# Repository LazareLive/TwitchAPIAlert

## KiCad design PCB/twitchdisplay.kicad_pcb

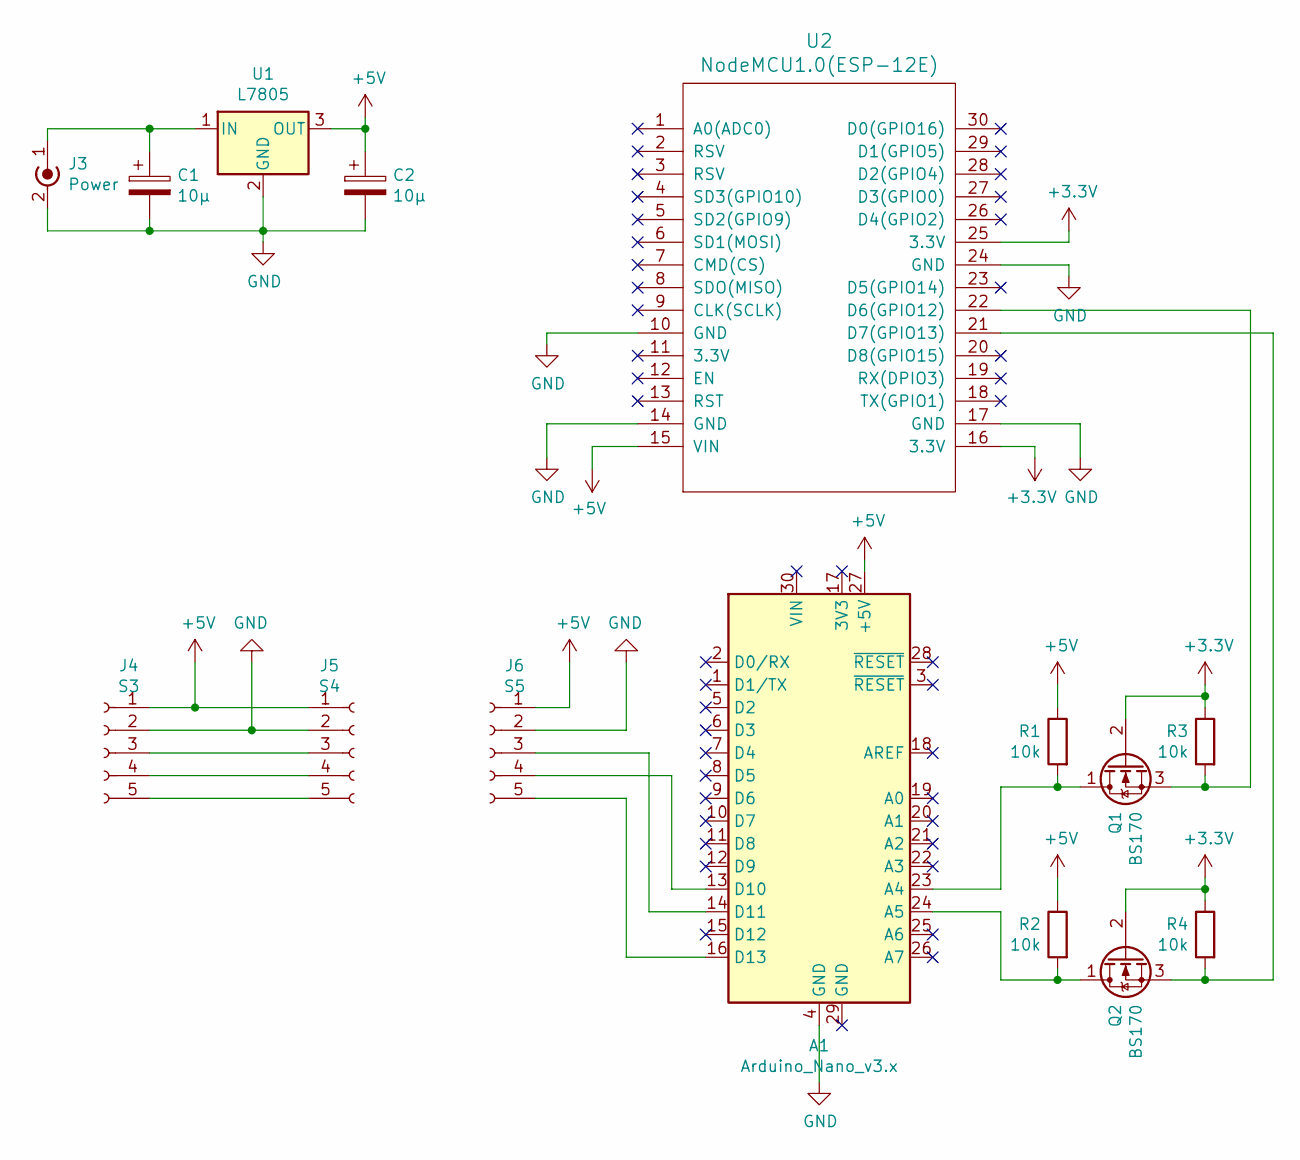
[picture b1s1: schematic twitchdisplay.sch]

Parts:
A1: Arduino_Nano_v3.x; Arduino_Nano
C1, C2: 10µ; CP_Radial_D5.0mm_P2.50mm
J3: Power; PinSocket_1x02_P2.54mm_Vertical
J4: S3; PinSocket_1x05_P2.54mm_Vertical
J5: S4; PinSocket_1x05_P2.54mm_Vertical
J6: S5; PinSocket_1x05_P2.54mm_Vertical
Q1, Q2: BS170; TO-92_Inline
R1, R2, R3, R4: 10k; R_Axial_DIN0207_L6.3mm_D2.5mm_P7.62mm_Horizontal
U1: L7805; TO-220-3_Horizontal_TabDown
U2: NodeMCU1.0(ESP-12E); NodeMCU1.0(12-E)

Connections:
+3V3: Q1.2 (G), Q2.2 (G), R3.1, R4.1, U2.16 (3.3V), U2.25 (3.3V)
+5V: A1.27 (+5V), C2.1, J4.1, J5.1, J6.1, R1.1, R2.1, U1.3 (OUT), U2.15 (VIN)
GND: A1.4 (GND), C1.2, C2.2, J3.2 (Ext), J4.2, J5.2, J6.2, U1.2 (GND), U2.10 (GND), U2.14 (GND), U2.17 (GND), U2.24 (GND)
unnamed: A1.13 (D10), J6.4
unnamed: A1.14 (D11), J6.3
unnamed: A1.16 (D13), J6.5
unnamed: A1.23 (A4), Q1.1 (D), R1.2
unnamed: A1.24 (A5), Q2.1 (D), R2.2
unnamed: C1.1, J3.1 (In), U1.1 (IN)
unnamed: J4.3, J5.3
unnamed: J4.4, J5.4
unnamed: J4.5, J5.5
unnamed: Q1.3 (S), R3.2, U2.22 (D6(GPIO12))
unnamed: Q2.3 (S), R4.2, U2.21 (D7(GPIO13))

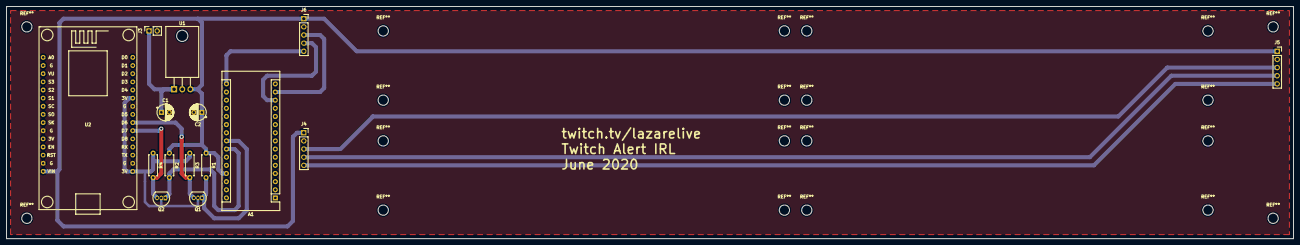
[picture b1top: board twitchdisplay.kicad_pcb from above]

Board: 2 copper layers, 401.3 x 72.4 mm, 15 parts (0 on the bottom side), 14 nets.
